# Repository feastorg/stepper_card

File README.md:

# stepper_card
Stepper Card for new stepper slice

# TODO
- [ ] Add SPI/I2C connectors (maybe QUIIC) for encoder for eventual closed loop control (or just move to Dsub or something all encompassing)
- [ ] Finalize board dimensions
- [ ] add mounting holes and other ways to secure mechanically

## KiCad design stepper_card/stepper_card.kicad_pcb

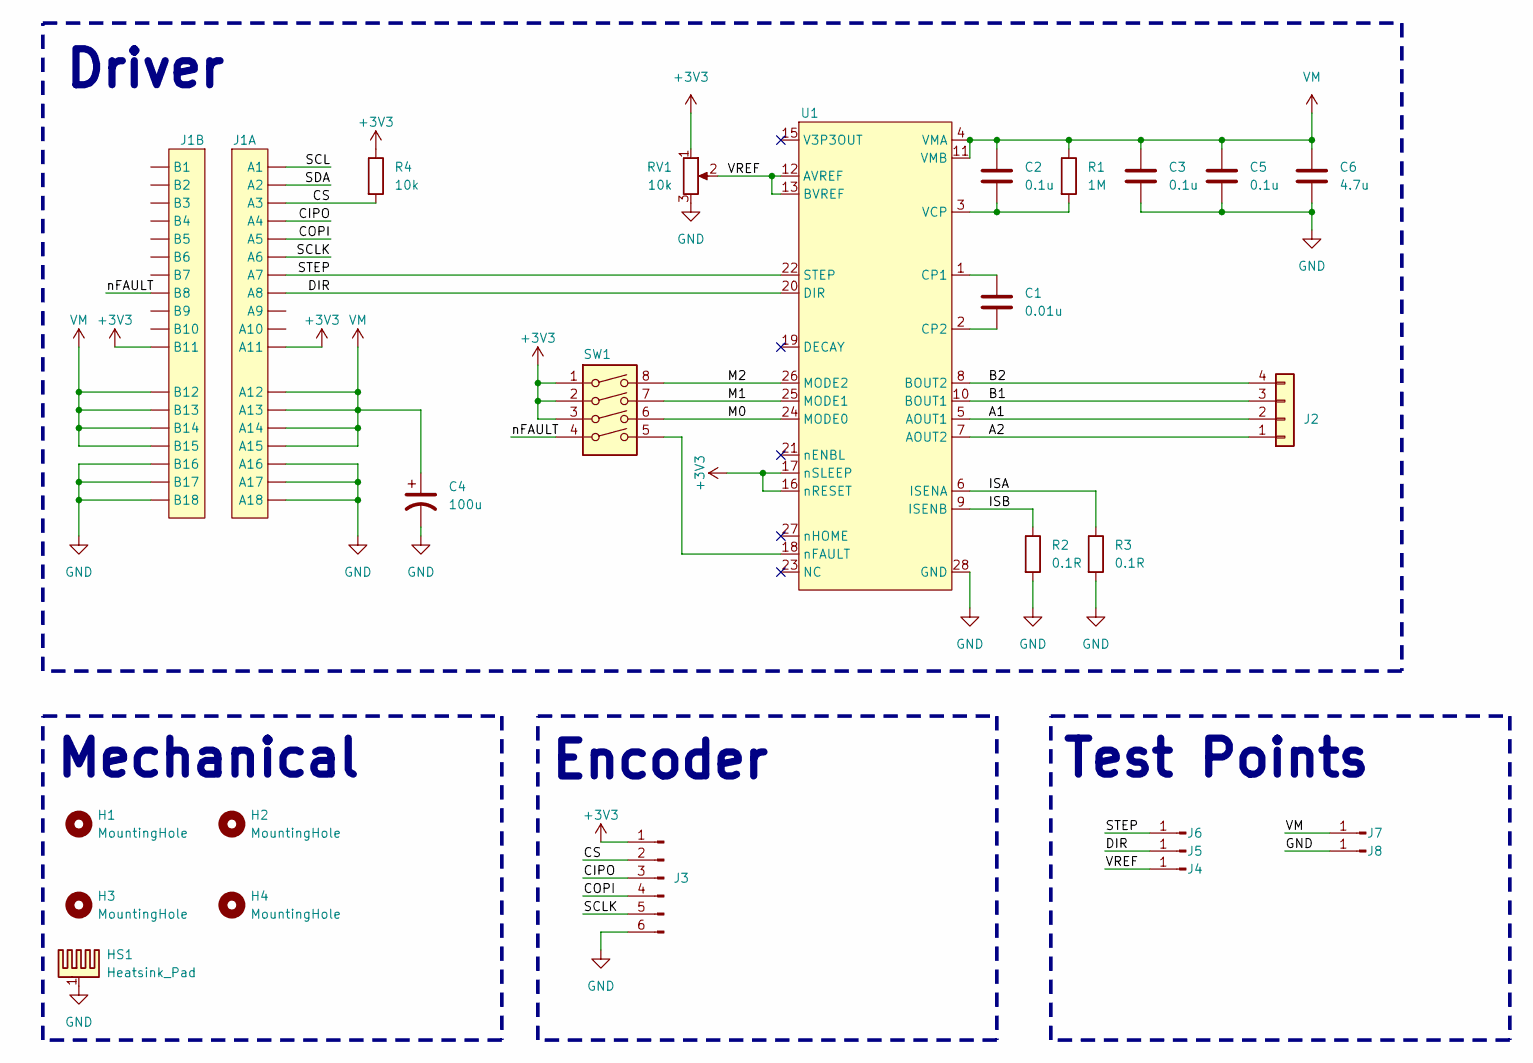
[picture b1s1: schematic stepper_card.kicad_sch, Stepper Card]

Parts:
C1: 0.01u; C_0603_1608Metric_Pad1.08x0.95mm_HandSolder
C2, C3, C5: 0.1u; C_0603_1608Metric_Pad1.08x0.95mm_HandSolder
C4: 100u; CP_Elec_6.3x7.7
C6: 4.7u; C_0603_1608Metric_Pad1.08x0.95mm_HandSolder
H1, H2, H3, H4: MountingHole; MountingHole_5mm
HS1: Heatsink_Pad; Thermal Pad
J1: Bus_PCI_Express_x1; BUS_PCIexpress_x1
J2: Conn_01x04; JST_XH_S4B-XH-A-1_1x04_P2.50mm_Horizontal
J3: Conn_01x06_Pin; PinHeader_1x06_P2.54mm_Horizontal
J4, J5, J6, J7, J8: Conn_01x01_Pin; TestPoint_Pad_2.0x2.0mm
R1: 1M; R_0603_1608Metric_Pad0.98x0.95mm_HandSolder
R2, R3: 0.1R; R_0603_1608Metric_Pad0.98x0.95mm_HandSolder
R4: 10k; R_0201_0603Metric_Pad0.64x0.40mm_HandSolder
RV1: 10k; Potentiometer_Bourns_3266W_Vertical
SW1: SW_DIP_x04; SW_DIP_SPSTx04_Slide_9.78x12.34mm_W8.61mm_P2.54mm
U1: DRV8825PWPR_Stepper_Driver; HTSSOP-28-1EP_4.4x9.7mm_P0.65mm_EP2.75x6.2mm_ThermalVias

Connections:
+3V3: J1.A11, J1.B11, J3.1, R4.1, RV1.1, SW1.1, SW1.2, SW1.3, U1.16 (nRESET), U1.17 (nSLEEP)
/A1: J2.2, U1.5 (AOUT1)
/A2: J2.1, U1.7 (AOUT2)
/B1: J2.3, U1.10 (BOUT1)
/B2: J2.4, U1.8 (BOUT2)
/CIPO: J1.A4, J3.3
/COPI: J1.A5, J3.4
/CS: J1.A3, J3.2, R4.2
/DIR: J1.A8, J5.1, U1.20 (DIR)
/ISA: R3.1, U1.6 (ISENA)
/ISB: R2.1, U1.9 (ISENB)
/M0: SW1.6, U1.24 (MODE0)
/M1: SW1.7, U1.25 (MODE1)
/M2: SW1.8, U1.26 (MODE2)
/SCL: J1.A1
/SCLK: J1.A6, J3.5
/SDA: J1.A2
/STEP: J1.A7, J6.1, U1.22 (STEP)
/VREF: J4.1, RV1.2, U1.12 (AVREF), U1.13 (BVREF)
/nFAULT: J1.B8, SW1.4
GND: C3.2, C4.2, C5.2, C6.2, HS1.1, J1.A16, J1.A17, J1.A18, J1.B16, J1.B17, J1.B18, J3.6, J8.1, R2.2, R3.2, RV1.3, U1.14 (GND), U1.28 (GND), U1.29 (PPAD)
unnamed: C1.1, U1.1 (CP1)
unnamed: C1.2, U1.2 (CP2)
unnamed: C2.2, R1.2, U1.3 (VCP)
unnamed: SW1.5, U1.18 (nFAULT)
VM: C2.1, C3.1, C4.1, C5.1, C6.1, J1.A12, J1.A13, J1.A14, J1.A15, J1.B12, J1.B13, J1.B14, J1.B15, J7.1, R1.1, U1.4 (VMA), U1.11 (VMB)

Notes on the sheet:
Driver
Test Points
Mechanical
Encoder

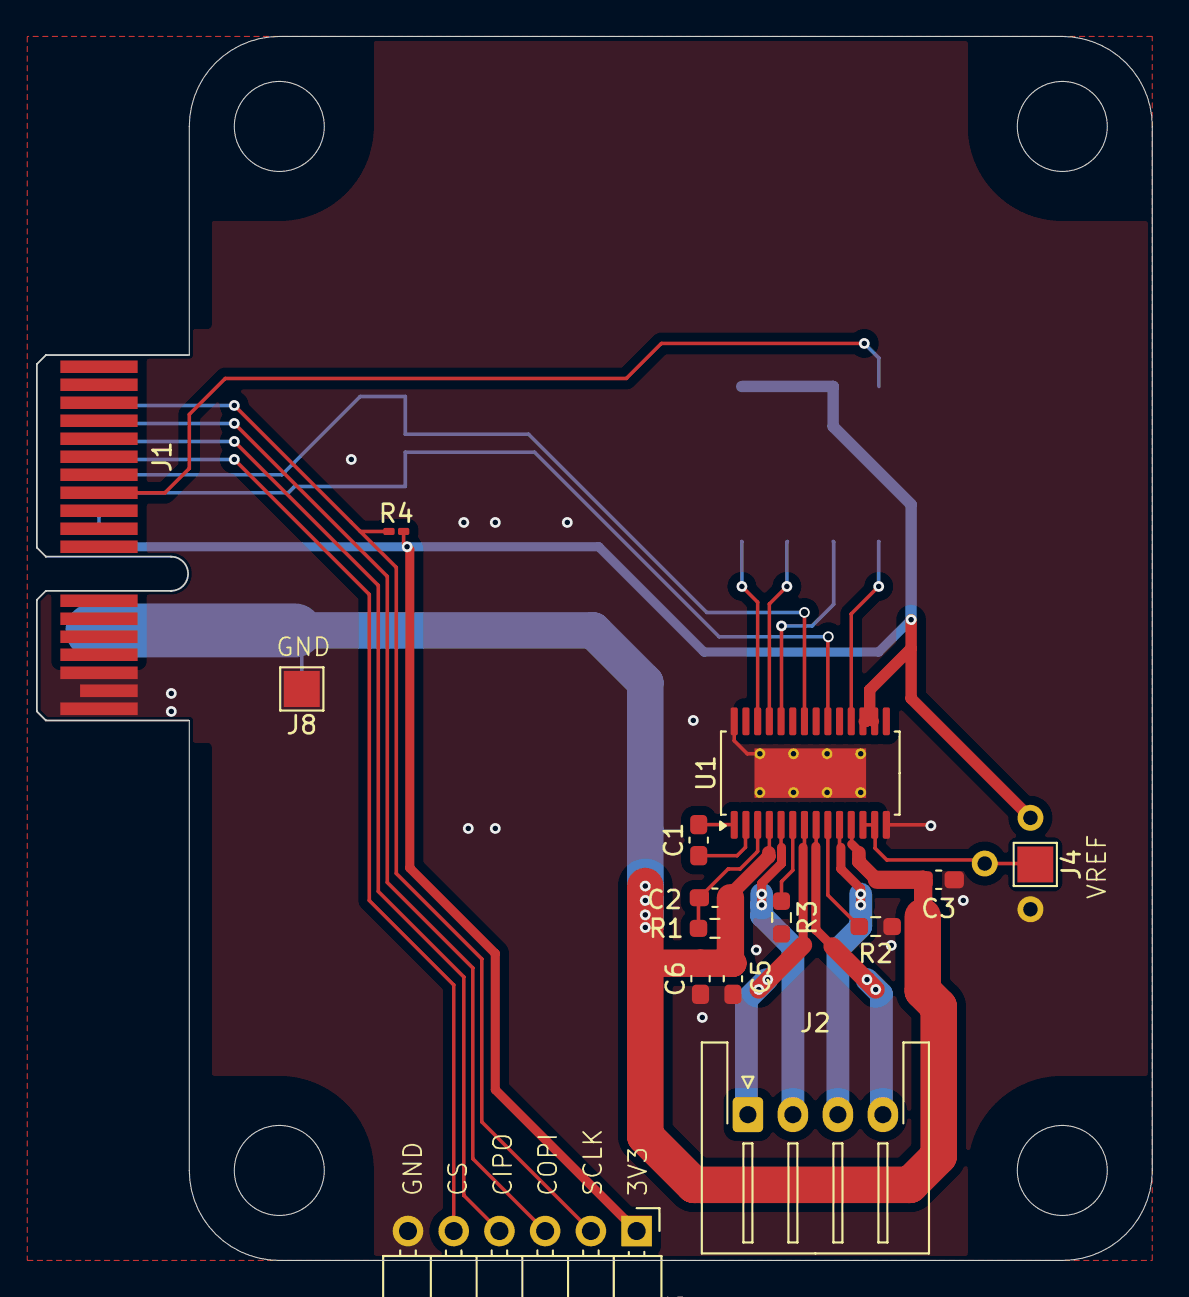
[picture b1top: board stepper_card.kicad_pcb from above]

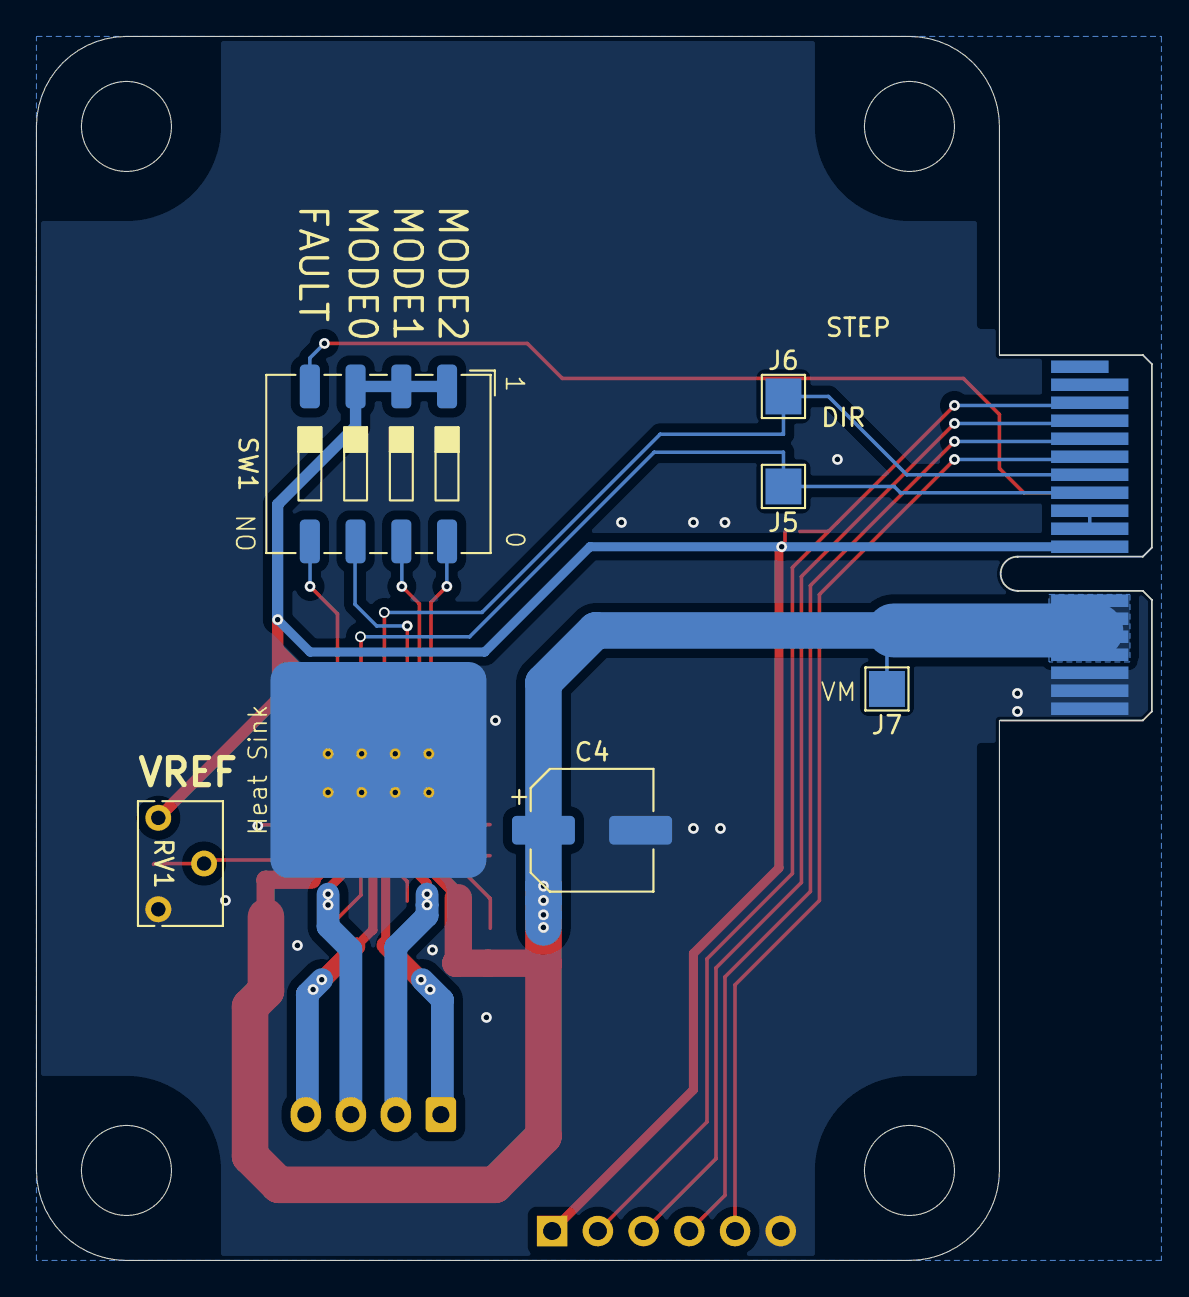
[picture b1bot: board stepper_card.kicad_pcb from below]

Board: 2 copper layers, 61.9 x 68.0 mm, 26 parts (7 on the bottom side), 24 nets.

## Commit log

2026-02-28 made files
2026-05-05 schematic and started layout
2026-05-05 added auto detection trace
2026-05-05 changed readme
2026-05-06 updated layout
2026-05-07 finished routing added test points
2026-05-07 routing complete
2026-05-07 routing
2026-05-21 changed pinout
2026-05-21 changed pinout on PCIE
2026-05-21 cleaned up schematic
2026-05-22 changed pinout and added pullup onto cs
2026-06-13 feat(grain): add grain.yaml manifest
2026-06-13 ci: add grain manifest validation workflow
2026-06-13 chore: add GPL-3.0 license
2026-06-13 chore: correct license to GPL-3.0-only, remove TODO comment
